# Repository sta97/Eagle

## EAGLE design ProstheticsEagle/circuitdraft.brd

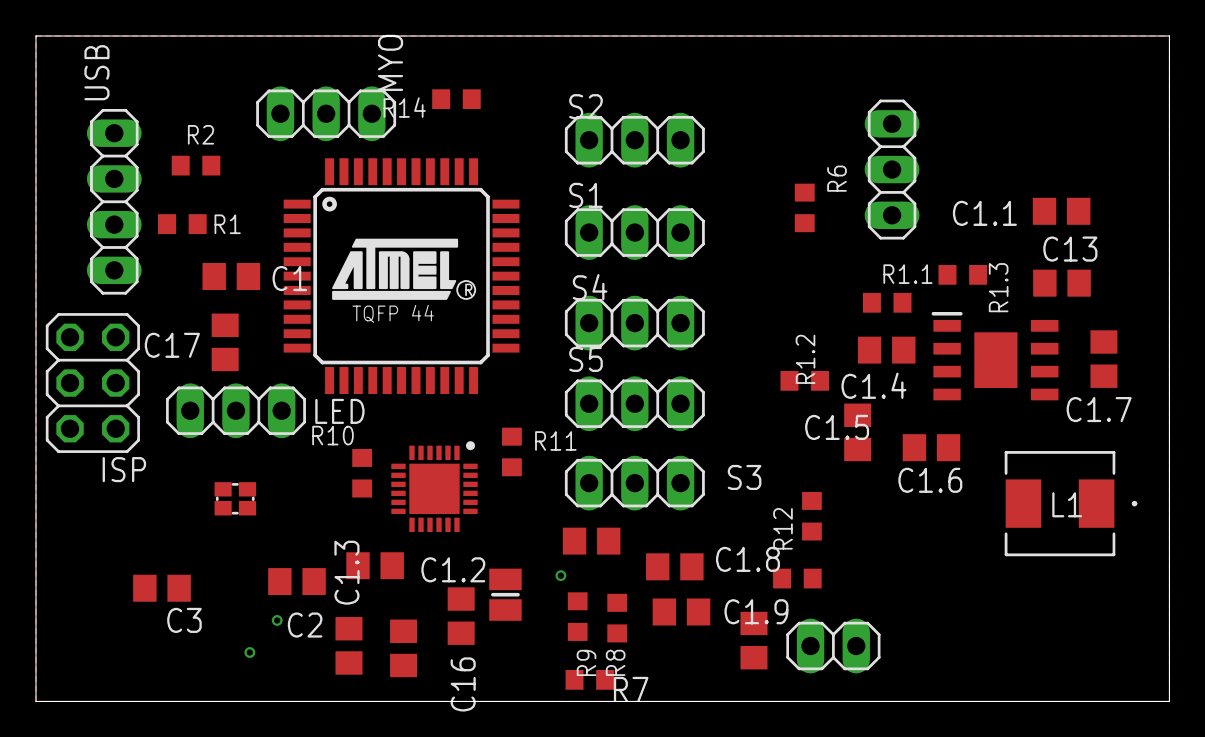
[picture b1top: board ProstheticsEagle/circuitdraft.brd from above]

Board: 2 copper layers, 63.0 x 37.0 mm, 49 parts (0 on the bottom side), 43 nets, no tracks yet.

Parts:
BATIO: 1X03
C1, C1.5, C13, C17: 1 uF; C0805
C1.1, C1.2, C18: 10 uF; C0805
C1.3: .1 uF; C0805
C1.4: 10 pF; C0805
C1.6: 8200 pF; C0805
C1.7: 0.1 uF; C0805
C1.8, C1.9: 22 uF; C0805
C2: 22pF; C0805
C3: 22 pF; C0805
C14: 4.7 uF; C0805
C15: 47 nF; C0805
C16: 44 uF; C0805
IC1: BQ25887RGER; QFN50P400X400X100-25N
IC2: TPS54627DDAR; SOIC127P600X170-9N
ISP: 2X03
L1: IHLP2020CZER3R3M01; IND_IHLP-2020CZ
L2: 1 uH; INDC2016X100N
LED: 1X03
MYO: 1X03
Q1: 16 MHz; 2.0X1.6_KX-5
R1, R2: 22 Ohms; R0603
R1.1: 124000 Ohms; R0603
R1.2: 22100 Ohms; R0603
R1.3, R7, R8, R9, R10, R11: 10000 Ohms; R0603
R6: 12 Ohms; R0603
R12: 30.1 kOhms; R0603
R13: 5.23 kOhms; R0603
R14: 300 Ohms; R0603
S1, S2, S3, S4, S5: 1X03
TS: 1X02
U$1: ATMEGA32U4-AU; TQFP44
USB: 1X04

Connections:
AGND: BATIO.3, C1.2, C1.1.1, C1.2.1, C1.3.1, C1.5.2, C1.6.2, C1.8.2, C1.9.2, C2.1, C3.1, C13.1, C14.2, C16.2, C17.1, C18.2, IC1.8, IC1.20, IC2.5, IC2.9, ISP.6, LED.2, MYO.2, R1.2.2, R12.1, S1.3, S2.3, S3.3, S4.3, S5.3, TS.2, U$1.23
B+: BATIO.1, C1.1.2, C1.2.2, C1.3.2, C13.2, IC1.13, IC2.8, R1.3.1
BTST: C15.2, IC1.12
D+: R1.1, USB.2
D-: R2.1, USB.3
DATAIN: LED.3, U$1.12
INT: IC1.6, R10.1, U$1.25
MIDDLE: BATIO.2, R6.1, R14.1, U$1.36
MISO: ISP.1, U$1.11
MOSI: ISP.4, U$1.10
MYOSIGNAL: MYO.3, U$1.41
unnamed: IC2.1, R1.3.2
unnamed: R2.2, U$1.3
unnamed: IC1.10, R6.2
unnamed: R1.2, U$1.4
unnamed: C3.2, Q1.1, U$1.16
unnamed: C2.2, Q1.3, U$1.17
unnamed: IC1.1, R9.1
unnamed: C1.1, U$1.6
unnamed: C1.6.1, IC2.4
unnamed: IC1.9, R14.2
unnamed: C1.4.1, IC2.2, R1.1.2, R1.2.1
unnamed: C1.5.1, IC2.3
unnamed: C1.7.1, IC2.6, L1.2
unnamed: C1.7.2, IC2.7
unnamed: C15.1, IC1.17, L2.2
unnamed: C14.1, IC1.11, R13.2
unnamed: C16.1, IC1.15
unnamed: C18.1, IC1.21, L2.1
POWER: C1.4.2, C1.8.1, C1.9.1, ISP.2, L1.1, LED.1, MYO.1, R1.1.1, S1.2, S2.2, S3.2, S4.2, S5.2, U$1.2, U$1.14, U$1.24
RST: ISP.5, U$1.13
SCK: ISP.3, U$1.9
SCL: IC1.5, R8.1, U$1.18
SDA: IC1.4, R7.1, U$1.19
SIGNAL1: S1.1, U$1.29
SIGNAL2: S2.1, U$1.30
SIGNAL3: S3.1, U$1.32
SIGNAL4: S4.1, U$1.31
SIGNAL5: S5.1, U$1.27
STAT: IC1.2, R11.1, U$1.26
TS: IC1.7, R12.2, R13.1, TS.1
UGND: U$1.5, USB.4
VBUS: C17.2, IC1.23, IC1.24, R7.2, R8.2, R9.2, R10.2, R11.2, U$1.7, USB.1

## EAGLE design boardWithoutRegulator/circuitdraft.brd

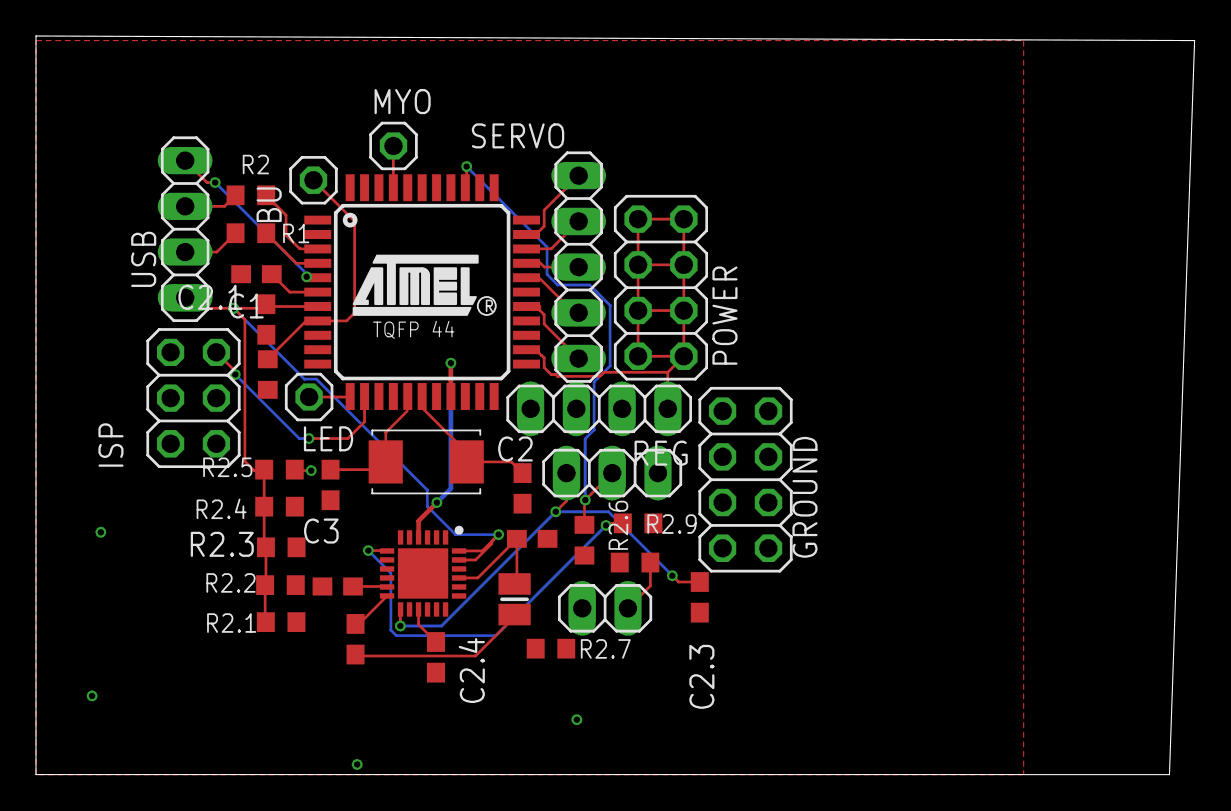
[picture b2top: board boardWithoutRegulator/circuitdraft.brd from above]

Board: 2 copper layers, 64.4 x 41.0 mm, 36 parts (0 on the bottom side), 38 nets.

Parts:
BATIO: 1X03
BU: 1X01
C1, C2.1, C2.3: 1 uF; C0603
C2: 22pF; C0603
C2.2: 4.7 uF; C0603
C2.4: 44 uF; C0603
C2.5: 47 nF; C0603
C2.6: 10 uF; C0603
C3: 22 pF; C0603
GROUND: 2X04
IC1: BQ25887RGER; QFN50P400X400X100-25N
ISP: 2X03
L2: 1 uH; INDC2016X100N
LED: 1X01
MYO: 1X01
POWER: 2X04
Q1: 16 MHz; ECS2501823GJGNTR
R1, R2: 22 Ohms; R0603
R2.1, R2.2, R2.3, R2.4, R2.5: 10000 Ohms; R0603
R2.6: 300 Ohms; R0603
R2.7: 12 Ohms; R0603
R2.8: 5.23 kOhms; R0603
R2.9: 30.1 kOhms; R0603
RBUTTON: 220 Ohm; R0603
REG: 1X04
SERVO: 1X05
TS: 1X02
U$1: ATMEGA32U4-AU; TQFP44
USB: 1X04

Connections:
B+: BATIO.1, C2.3.2, IC1.13, REG.3
BTST: C2.5.2, IC1.12
D+: R1.1, USB.2
D-: R2.1, USB.3
DATAIN: LED.1, U$1.12
GND: BATIO.3, C1.2, C2.1, C2.1.1, C2.2.2, C2.3.1, C2.4.2, C2.6.2, C3.1, GROUND.1, GROUND.2, GROUND.3, GROUND.4, GROUND.5, GROUND.6, GROUND.7, GROUND.8, IC1.8, IC1.20, IC1.25, ISP.6, R2.9.1, RBUTTON.2, REG.2, TS.2, U$1.23
INT: IC1.6, R2.1.1, U$1.25
INTERRUPT: BU.1, RBUTTON.1, U$1.8
MIDDLE: BATIO.2, R2.6.1, R2.7.1, U$1.36
MISO: ISP.1, U$1.11
MOSI: ISP.4, U$1.10
MYOSIGNAL: MYO.1, U$1.41
unnamed: R2.2, U$1.3
unnamed: IC1.10, R2.7.2
unnamed: R1.2, U$1.4
unnamed: C3.2, Q1.1, U$1.16
unnamed: C2.2, Q1.2, U$1.17
unnamed: IC1.1, R2.5.1
unnamed: C1.1, U$1.6
unnamed: IC1.9, R2.6.2
unnamed: C2.5.1, IC1.17, L2.2
unnamed: C2.2.1, IC1.11, R2.8.2
unnamed: C2.4.1, IC1.15
unnamed: C2.6.1, IC1.21, L2.1
POWER: ISP.2, POWER.1, POWER.2, POWER.3, POWER.4, POWER.5, POWER.6, POWER.7, POWER.8, REG.1, U$1.2, U$1.14, U$1.24
RST: ISP.5, U$1.13
SCK: ISP.3, U$1.9
SCL: IC1.5, R2.2.1, U$1.18
SDA: IC1.4, R2.3.1, U$1.19
SIGNAL1: SERVO.4, U$1.29
SIGNAL2: SERVO.3, U$1.30
SIGNAL3: SERVO.1, U$1.32
SIGNAL4: SERVO.2, U$1.31
SIGNAL5: SERVO.5, U$1.27
STAT: IC1.2, R2.4.1, U$1.26
TS: IC1.7, R2.8.1, R2.9.2, TS.1
UGND: U$1.5, USB.4
VBUS: C2.1.2, IC1.23, IC1.24, R2.1.2, R2.2.2, R2.3.2, R2.4.2, R2.5.2, U$1.7, USB.1

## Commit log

2019-10-29 Starting out 10/29/2019
2019-11-01 This is a test
2019-11-01 Removed unnecessary things
2019-11-08 Semi-complete schematic and auto routed board
2019-11-08 Deleted dumb stuff
2019-11-08 reste
2019-11-10 Added surface mount parts
2019-11-11 fffff
2019-11-11 removed stuff
2019-11-11 moved stuff
2019-11-11 Ahmad's revision
2019-11-11 ahmad's changes?
2019-11-11 ffff
2019-11-14 added new inductor
2019-11-14 Put things closer to closer
2019-11-15 Reorganized alot of things. Created different grounds
2019-11-15 Ahmad's changes
2019-11-18 Started to route and made power more centralized
2019-11-18 This probably did not work
2019-11-18 More Routing
2019-11-18 Routhing
2019-11-18 Finished routuing?
2019-11-18 Ahmad's suggestions
2019-11-18 Fixed it boii
2019-11-20 Added plan B
2019-11-20 using external board for charging, removes regulator, needs tweaking
2019-11-20 added regulator
2019-11-20 ajusted to thorugh whole parts
2019-11-20 fixed orientation of regulator connections
2019-11-20 shifted regulator to ensure enough spacing between daughterboards

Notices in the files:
parts and their libraries:
crystal-geyer_V1_0: Copyright: Geyer-Electronic
